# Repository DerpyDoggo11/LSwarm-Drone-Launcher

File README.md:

# LS Mk.1 Drone Launcher
Compact drone launcher + central compute module

## 3D Model Preview

## 3D PCB Preview

## Wiring

## Schematic

### Download ./latestProduction to begin fabricating the PCB

## Introduction
As a solution to needing to store tons of [these](https://forge.hackclub.com/projects/93) microdrones as well as the central compute unit, I designed a vertically mounting lift off platform and storage unit called the LS Mk.1 Drone Launcher. Its super modular so that it can be stacked on itself and easily stored in a grid and scale to any number of drones. The design is essentially a 3D printed platform with four metal rods for guiding the drones, the top and bottom half can separated or connected by opening or closing the latches. The platform currently has a capacity for 5 drones each.

For calculating and planning the trajectory of the drones, this launcher uses a Raspbbery Pi Zero 2 W along with a custom Pi hat. The custom Pi hat extends the wifi range of the Raspberry Pi Zero 2 W to communicate with the LS Anchors and adds a battery for independent usage from wall outlets. Only 1 compute module should be necessary per batch of launcher units.

## Bill of Materials 

### Minimum Build:

| Quantity | Components | Price | Link |
|--------- |----------|----------| -----|
| 1  | Raspberry Pi Zero 2 W | ~15$ | [here](https://www.sparkfun.com/raspberry-pi-zero-2-w.html?src=raspberrypi)
| 1 | Clear PLA Filament | ~20$ | [here](https://www.amazon.com/SUNLU-Filament-Transparent-Dimensional-Accuracy/dp/B07ZNG4L9P?channelId=520&clpRedir=Y&dib=eyJ2IjoiMSJ9._Y4kmvLmwjvktiYmXwsyz_Am5xx7NReuKA_k9fHzIejFf9UoUlhPqIUR2Kfcu_mx67XBB3snagQ-fa1A_Ys3FWvcWoi1dI5MsJ6hGMeDpd1BIR1tq_-gIXaTG5BrTvI7VzTtiaEztBTeRebkZxvTPw4tFbMlbzCpfKi1du8ktHhgZnWP9pK3flO77HIb2ggK4b0B9uJqkWQFQodsriMgJxH84ljwj4H8OITJnoYh_vE.2zkivrb0O9D5yNAwScLuwbLs3Lk4bP8leoBIEJbwXRQ&dib_tag=se&keywords=transparent%2Bpla&plpRedirect=mhFallback&qid=1785305371&sr=8-4&th=1)
| 1 | 1200mAh Lipo Battery | ~20$ [here](https://www.aliexpress.us/item/3256811414820649.html?spm=a2g0o.productlist.main.1.46bdwH3SwH3Sbj&algo_pvid=cdb969a2-c563-41ce-bc78-12d1dc257c78&algo_exp_id=cdb969a2-c563-41ce-bc78-12d1dc257c78-0&pdp_ext_f=%7B%22order%22%3A%2296%22%2C%22eval%22%3A%221%22%2C%22fromPage%22%3A%22search%22%7D&pdp_npi=6%40dis%21USD%2111.31%216.16%21%21%2176.16%2141.49%21%402101d3fe17841520345512246e1288%2112000056027143357%21sea%21US%217493938711%21X%211%210%21n_tag%3A-29919%3Bd%3Ad260408f%3Bm03_new_user%3A-29895%3BpisId%3A5000000211679188&curPageLogUid=uhXJ9YqKgNaO&utparam-url=scene%3Asearch%7Cquery_from%3A%7Cx_object_id%3A1005011601135401%7C_p_origin_prod%3A)
| 1 | 155mm Leather Handle | ~2$ | [here](https://www.aliexpress.us/item/3256812155687340.html?spm=a2g0o.productlist.main.15.27dajTuqjTuqFp&algo_pvid=e87958b2-7cc6-45ee-9165-c5cc9b5004c7&algo_exp_id=e87958b2-7cc6-45ee-9165-c5cc9b5004c7-14&pdp_ext_f=%7B%22order%22%3A%221%22%2C%22eval%22%3A%221%22%2C%22fromPage%22%3A%22search%22%7D&pdp_npi=6%40dis%21USD%211.72%211.02%21%21%2111.56%216.84%21%402101e5ab17852684858322898e0dcb%2112000058138770576%21sea%21US%210%21ABX%211%210%21n_tag%3A-29910%3Bd%3Ad260408f%3Bm03_new_user%3A-29895%3BpisId%3A5000000210913316&curPageLogUid=BP5HyM53Apva&utparam-url=scene%3Asearch%7Cquery_from%3A%7Cx_object_id%3A1005012342002092%7C_p_origin_prod%3A)
| 4 | 200mm x 4mm Metal Rods | $5 | [here](https://www.aliexpress.us/item/3256805290944526.html?spm=a2g0o.productlist.main.3.2df5s35ms35mOY&algo_pvid=af55ae4c-899e-4dcc-919f-7cc0f6e58495&algo_exp_id=af55ae4c-899e-4dcc-919f-7cc0f6e58495-2&pdp_ext_f=%7B%22order%22%3A%224031%22%2C%22eval%22%3A%221%22%2C%22fromPage%22%3A%22search%22%7D&pdp_npi=6%40dis%21USD%212.22%212.15%21%21%2114.95%2114.51%21%402101de2517853088871028484e0d56%2112000033239843707%21sea%21US%217493938711%21X%211%210%21n_tag%3A-29919%3Bd%3Ad260408f%3Bm03_new_user%3A-29895&curPageLogUid=mLtoWIDfhah6&utparam-url=scene%3Asearch%7Cquery_from%3A%7Cx_object_id%3A1005005477259278%7C_p_origin_prod%3A)
| 1  | RPI Hat PCB | ~15$ | Download repo, extract fabrication files, and fabricate through JLCPCB (complete instructions for this may come soon)
| 1  | Electronic Components | ~30$ | See production BOM for a full list, the PCB fabrication files automatically include these components as well.
| 4 | 20mm M2.5 Bolts | $10 | Reference (can find it cheaper elsewhere): [here](https://www.mcmaster.com/products/91290a108/)
| 16 | 16mm M2.5 Bolts | $10 | Reference (can find it cheaper elsewhere): [here](https://www.mcmaster.com/products/91290A106/)
| 20 | M2.5 Nuts | $10 | Reference (can find it cheaper elsewhere): [here](https://www.mcmaster.com/products/90591a270/)

Total: ~$140

----

## Tools / Other parts:
- Hot air gun or hot plate
- Solder paste
- Tweazers
- Screwdriver

## Assembly
- Apply solder paste to all the solder pads
- Use tweazers to place components and reflow with hot air gun or hot plate
- Assemble control unit case and mount battery and antenna onto the pcb and raspbbery pi zero 2W
- Print all parts of the case
- Assemble the launcher case and latch together
- Print drone landing gears and mount them

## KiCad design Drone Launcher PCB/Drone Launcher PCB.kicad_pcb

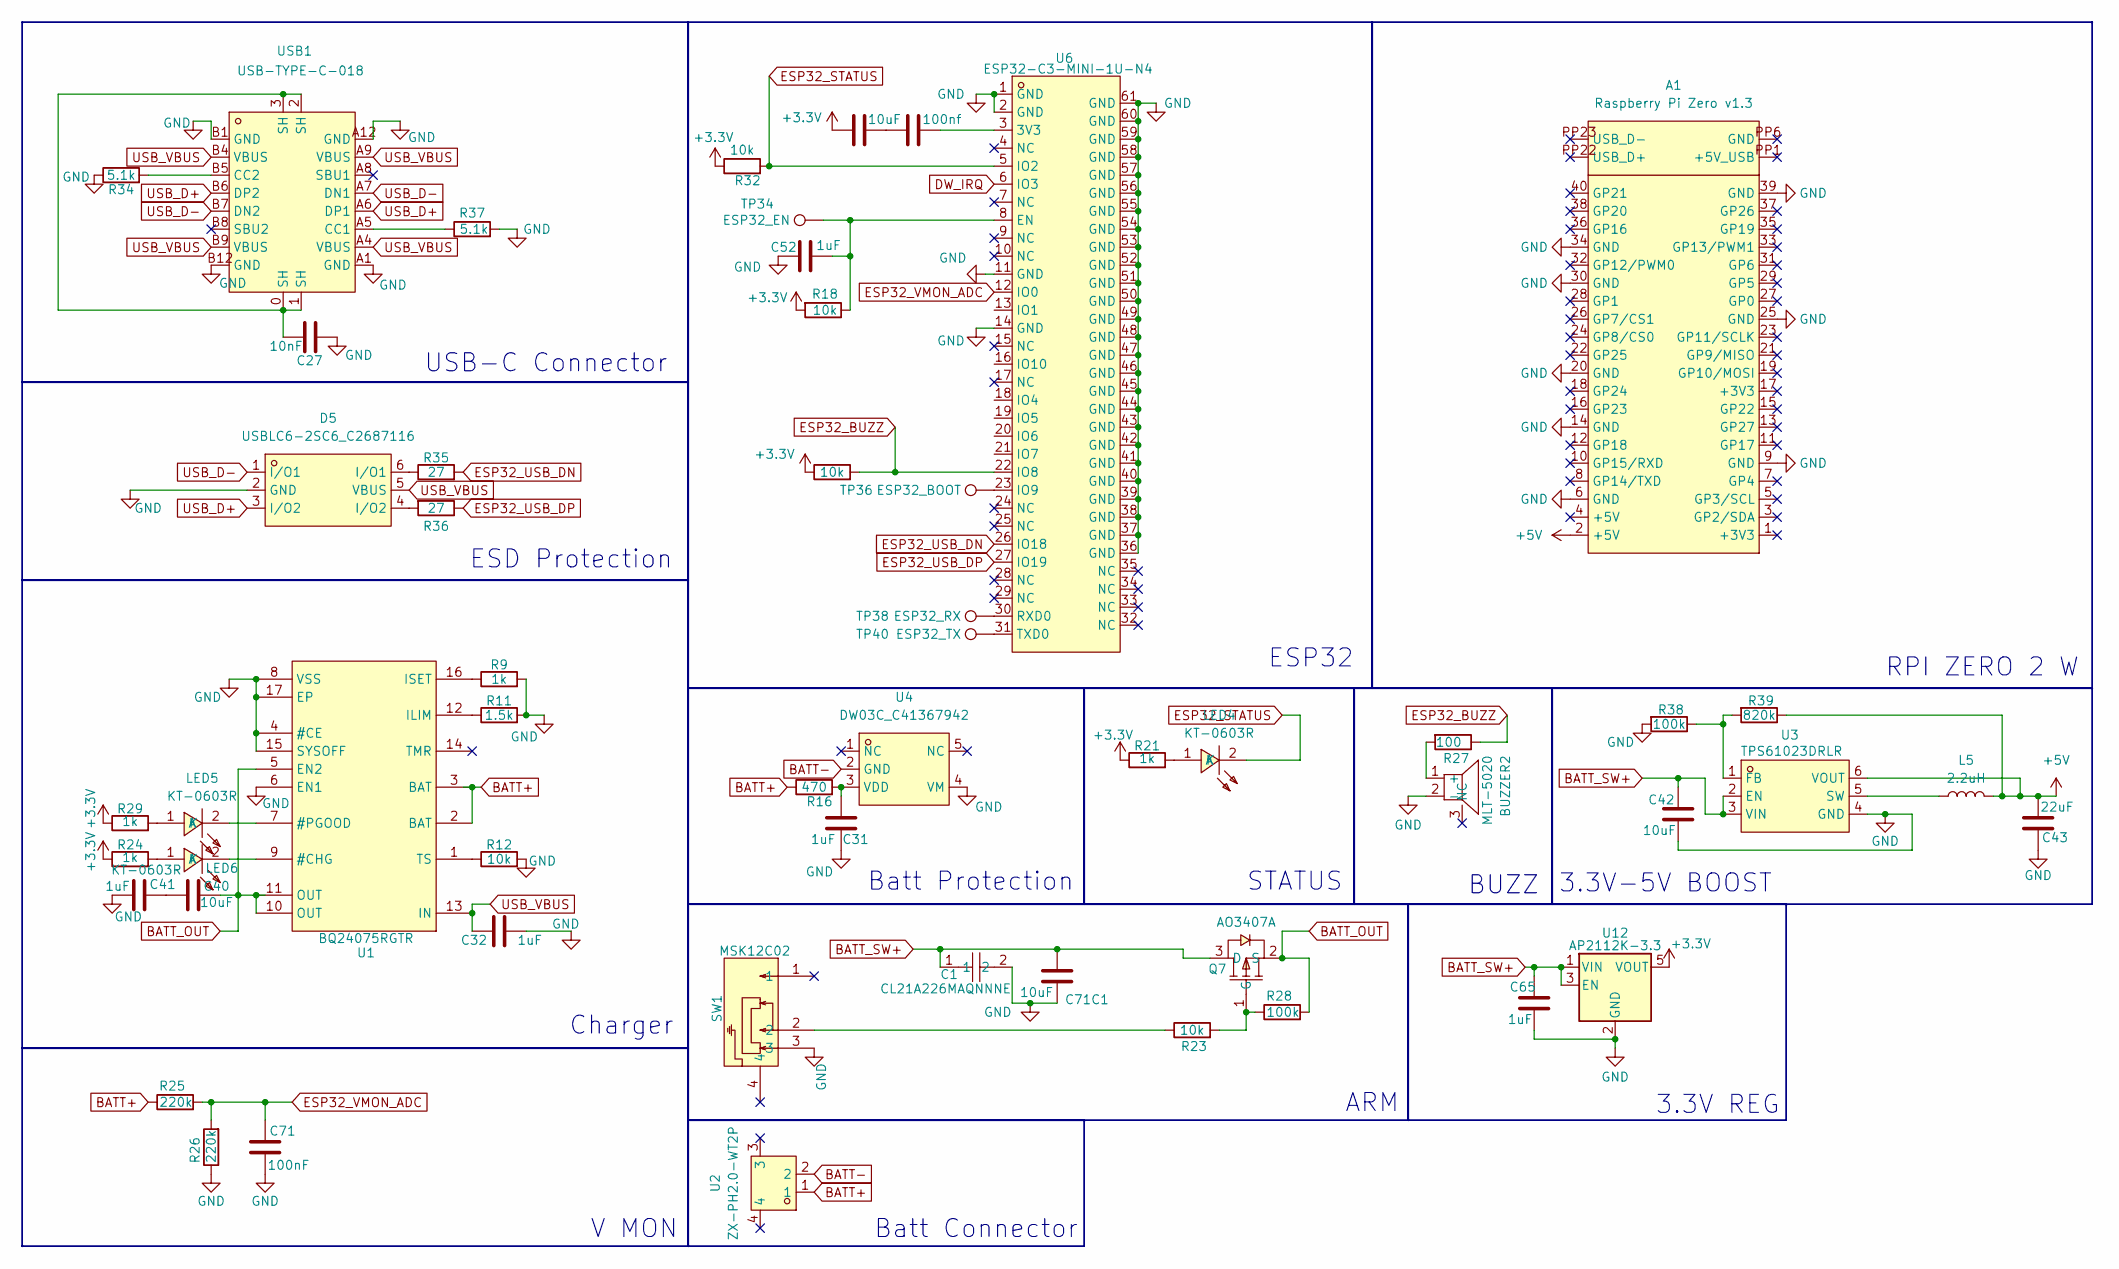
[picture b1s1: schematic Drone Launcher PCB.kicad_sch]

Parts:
A1: Raspberry Pi Zero v1.3; RASPI_ZERO_FULL
BUZZER2: MLT-5020; BUZ-SMD_L5.0-W5.5-P4.60; MPN MLT-5020; LCSC Part C94598
C1: CL21A226MAQNNNE; C0805; MPN CL21A226MAQNNNE; LCSC Part C45783
C27: 10nF; C_0603_1608Metric
C31, C32, C41, C52, C65: 1uF; C_0603_1608Metric
C40, C55: 10uF; C_0603_1608Metric
C42, C71C1: 10uF; C_0805_2012Metric
C43: 22uF; C_0805_2012Metric
C56: 100nf; C_0603_1608Metric
C71: 100nF; C_0603_1608Metric
D5: USBLC6-2SC6_C2687116; SOT-23-6_L2.9-W1.6-P0.95-LS2.8-BL; MPN USBLC6-2SC6; LCSC Part C2687116
L5: 2.2uH; L_1210_3225Metric
LED4, LED5, LED6: KT-0603R; LED-SMD_L1.6-W0.8-R-RD; MPN KT-0603R; LCSC Part C2286
Q7: AO3407A; SOT-23-3_L2.9-W1.6-P1.90-LS2.8-BR; MPN AO3407A; LCSC Part C15155
R9, R21, R24, R29: 1k; R_0603_1608Metric
R11: 1.5k; R_0603_1608Metric
R12, R18, R23, R32, R33: 10k; R_0603_1608Metric
R16: 470; R_0603_1608Metric
R25, R26: 220k; R_0603_1608Metric
R27: 100; R_0603_1608Metric
R28, R38: 100k; R_0603_1608Metric
R34, R37: 5.1k; R_0603_1608Metric
R35, R36: 27; R_0603_1608Metric
R39: 820k; R_0603_1608Metric
SW1: MSK12C02; SW-TH_MSK12C02; MPN MSK12C02; LCSC Part C431540
TP34: ESP32_EN; TestPoint_Pad_1.0x1.0mm
TP36: ESP32_BOOT; TestPoint_Pad_1.0x1.0mm
TP38: ESP32_RX; TestPoint_Pad_1.0x1.0mm
TP40: ESP32_TX; TestPoint_Pad_1.0x1.0mm
U1: BQ24075RGTR; QFN-16_L3.0-W3.0-P0.50-TL-EP1.7; MPN BQ24075RGTR; LCSC Part C15464
U2: ZX-PH2.0-WT2P; CONN-SMD_ZX-PH2.0-WT2P; MPN ZX-PH2.0-WT2P; LCSC Part C7429689
U3: TPS61023DRLR; SOT-563_L1.6-W1.2-P0.50-LS1.6-BR; MPN TPS61023DRLR; LCSC Part C919459
U4: DW03C_C41367942; SOT-23-5_L2.9-W1.6-P0.95-LS2.9-BL; MPN DW03C; LCSC Part C41367942
U6: ESP32-C3-MINI-1U-N4; WIFIM-SMD_61P-L13.2-W12.5-P0.80; MPN ESP32-C3-MINI-1U-N4; LCSC Part C2911374
U12: AP2112K-3.3; SOT-23-5
USB1: USB-TYPE-C-018; USB-C_SMD-TYPE-C-31-M-12; MPN USB-TYPE-C-018; LCSC Part C2927038

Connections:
+3.3V: C55.2, R18.2, R21.1, R24.1, R29.1, R32.1, R33.1, U12.5 (VOUT)
+5V: A1.2 (+5V), C43.2, L5.2, R39.1, U3.6 (VOUT)
BATT+: R16.1, R25.1, U1.2 (BAT), U1.3 (BAT), U2.1
BATT-: U2.2, U4.2 (GND)
BATT_OUT: C40.1, Q7.2 (S), R28.2, U1.5 (EN2), U1.10 (OUT), U1.11 (OUT)
BATT_SW+: C1.1, C42.1, C65.2, C71C1.2, Q7.3 (D), U3.2 (EN), U3.3 (VIN), U12.1 (VIN), U12.3 (EN)
DW_IRQ: U6.6 (IO3)
ESP32_BUZZ: R27.1, R33.2, U6.22 (IO8)
ESP32_STATUS: LED4.2 (K), R32.2, U6.5 (IO2)
ESP32_USB_DN: R35.2, U6.26 (IO18)
ESP32_USB_DP: R36.1, U6.27 (IO19)
ESP32_VMON_ADC: C71.2, R25.2, R26.2, U6.12 (IO0)
GND: A1.6 (GND), A1.9 (GND), A1.14 (GND), A1.20 (GND), A1.25 (GND), A1.30 (GND), A1.34 (GND), A1.39 (GND), BUZZER2.2 (-), C1.2, C27.1, C31.2, C32.1, C41.1, C42.2, C43.1, C52.1, C65.1, C71.1, C71C1.1, D5.2 (GND), R9.2, R11.2, R12.2, R26.1, R34.1, R37.2, R38.2, SW1.3, U1.4 (#CE), U1.6 (EN1), U1.8 (VSS), U1.15 (SYSOFF), U1.17 (EP), U3.4 (GND), U4.4 (VM), U6.1 (GND), U6.2 (GND), U6.11 (GND), U6.14 (GND), U6.36 (GND), U6.37 (GND), U6.38 (GND), U6.39 (GND), U6.40 (GND), U6.41 (GND), U6.42 (GND), U6.43 (GND), U6.44 (GND), U6.45 (GND), U6.46 (GND), U6.47 (GND), U6.48 (GND), U6.49 (GND), U6.50 (GND), U6.51 (GND), U6.52 (GND), U6.53 (GND), U6.54 (GND), U6.55 (GND), U6.56 (GND), U6.57 (GND), U6.58 (GND), U6.59 (GND), U6.60 (GND), U6.61 (GND), U12.2 (GND), USB1.A1 (GND), USB1.A12 (GND), USB1.B1 (GND), USB1.B12 (GND)
unnamed: BUZZER2.1 (+), R27.2
unnamed: C27.2, USB1.0 (SH), USB1.1 (SH), USB1.2 (SH), USB1.3 (SH)
unnamed: C40.2, C41.2
unnamed: C55.1, C56.2
unnamed: D5.6 (I/O1), R35.1
unnamed: D5.4 (I/O2), R36.2
unnamed: LED4.1 (A), R21.2
unnamed: LED5.1 (A), R29.2
unnamed: LED5.2 (K), U1.7 (#PGOOD)
unnamed: LED6.1 (A), R24.2
unnamed: LED6.2 (K), U1.9 (#CHG)
unnamed: Q7.1 (G), R23.2, R28.1
unnamed: R23.1, SW1.2
unnamed: R11.1, U1.12 (ILIM)
unnamed: R9.1, U1.16 (ISET)
unnamed: R12.1, U1.1 (TS)
unnamed: R38.1, R39.2, U3.1 (FB)
unnamed: L5.1, U3.5 (SW)
unnamed: C31.1, R16.2, U4.3 (VDD)
unnamed: C56.1, U6.3 (3V3)
unnamed: C52.2, R18.1, TP34.1 (1_1), U6.8 (EN)
unnamed: TP36.1 (1_1), U6.23 (IO9)
unnamed: TP38.1 (1_1), U6.30 (RXD0)
unnamed: TP40.1 (1_1), U6.31 (TXD0)
unnamed: R37.1, USB1.A5 (CC1)
unnamed: R34.2, USB1.B5 (CC2)
USB_D+: D5.3 (I/O2), USB1.A6 (DP1), USB1.B6 (DP2)
USB_D-: D5.1 (I/O1), USB1.A7 (DN1), USB1.B7 (DN2)
USB_VBUS: C32.2, D5.5 (VBUS), U1.13 (IN), USB1.A4 (VBUS), USB1.A9 (VBUS), USB1.B4 (VBUS), USB1.B9 (VBUS)

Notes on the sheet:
BUZZ
V MON
STATUS
RPI ZERO 2 W
ARM
USB-C Connector
3.3V REG
Batt Connector
ESP32
ESD Protection
3.3V-5V BOOST
Charger
Batt Protection

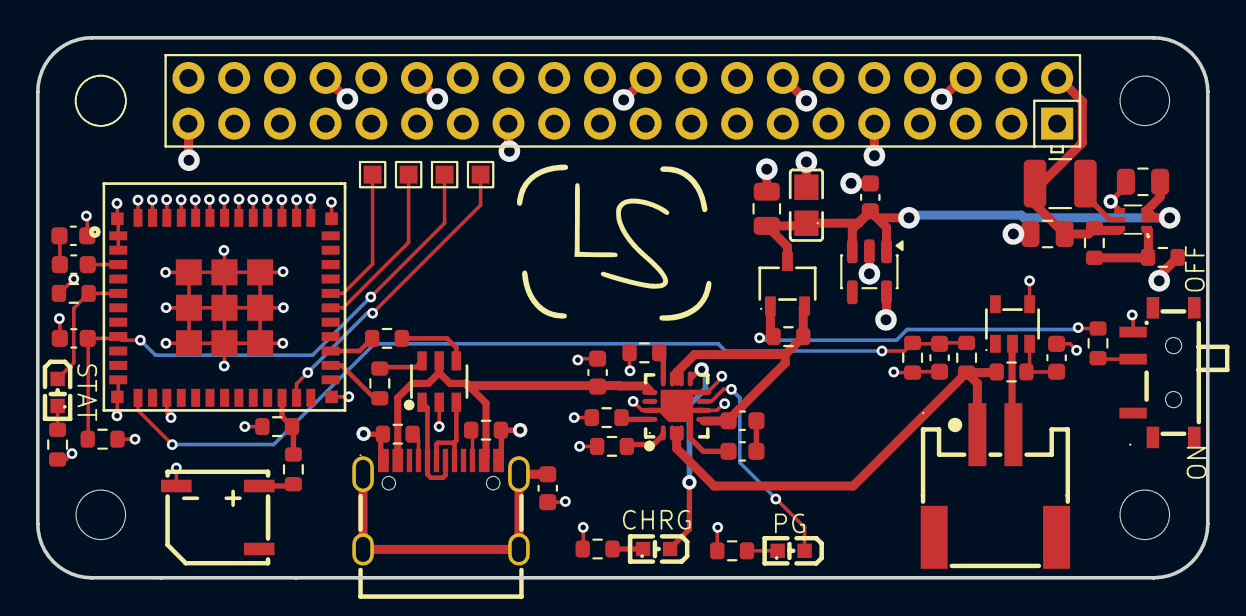
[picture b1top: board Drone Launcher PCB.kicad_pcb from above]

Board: 4 copper layers, 65.0 x 30.0 mm, 55 parts (0 on the bottom side), 41 nets.

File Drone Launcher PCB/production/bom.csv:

Designator,Footprint,Quantity,Value,LCSC Part #
A1,RASPI_ZERO_FULL,1,Raspberry Pi Zero v1.3,
BUZZER2,BUZ-SMD_L5.0-W5.5-P4.60,1,MLT-5020,C94598
C1,C0805,1,CL21A226MAQNNNE,C45783
C27,0603,1,10nF,
"C31, C32, C41, C52, C65",0603,5,1uF,
"C40, C55",0603,2,10uF,
"C42, C71C1",0805,2,10uF,
C43,0805,1,22uF,
"C56, C71",0603,2,100nf,
D5,SOT-23-6_L2.9-W1.6-P0.95-LS2.8-BL,1,USBLC6-2SC6_C2687116,C2687116
L5,1210,1,2.2uH,
"LED4, LED5, LED6",LED-SMD_L1.6-W0.8-R-RD,3,KT-0603R,C2286
Q7,SOT-23-3_L2.9-W1.6-P1.90-LS2.8-BR,1,AO3407A,C15155
R11,0603,1,1.5k,
"R12, R18, R23, R32, R33",0603,5,10k,
R16,0603,1,470,
"R21, R24, R29, R9",0603,4,1k,
"R25, R26",0603,2,220k,
R27,0603,1,100,
"R28, R38",0603,2,100k,
"R34, R37",0603,2,5.1k,
"R35, R36",0603,2,27,
R39,0603,1,820k,
SW1,SW-TH_MSK12C02,1,MSK12C02,C431540
TP34,TestPoint_Pad_1.0x1.0mm,1,ESP32_EN,
TP36,TestPoint_Pad_1.0x1.0mm,1,ESP32_BOOT,
TP38,TestPoint_Pad_1.0x1.0mm,1,ESP32_RX,
TP40,TestPoint_Pad_1.0x1.0mm,1,ESP32_TX,
U1,QFN-16_L3.0-W3.0-P0.50-TL-EP1.7,1,BQ24075RGTR,C15464
U12,SOT-23-5,1,AP2112K-3.3,
U2,CONN-SMD_ZX-PH2.0-WT2P,1,ZX-PH2.0-WT2P,C7429689
U3,SOT-563_L1.6-W1.2-P0.50-LS1.6-BR,1,TPS61023DRLR,C919459
U4,SOT-23-5_L2.9-W1.6-P0.95-LS2.9-BL,1,DW03C_C41367942,C41367942
U6,WIFIM-SMD_61P-L13.2-W12.5-P0.80,1,ESP32-C3-MINI-1U-N4,C2911374
USB1,USB-C_SMD-TYPE-C-31-M-12,1,USB-TYPE-C-018,C2927038
